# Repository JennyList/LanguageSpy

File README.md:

# LanguageSpy
Open source code from Language Spy, [http://www.languagespy.com](http://www.languagespy.com)

The Hardware directory contains open source hardware projects.

The RaspberryPi directory contains code for the Raspberry Pi.

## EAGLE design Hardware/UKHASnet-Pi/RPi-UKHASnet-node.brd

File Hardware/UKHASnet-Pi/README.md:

# A HopeRF RFM69 board for the Raspberry Pi
This is a board to allow the [HopeRF RFM69](http://www.hoperf.com/rf_transceiver/modules/RFM69HW.html) RF modules to be interfaced to a Raspberry Pi. It can be used for experimenting with [UKHASnet](https://ukhas.net/), or just as an experimenting board in its own right for the RFM69 series.

###Files:
- RPi-UKHASnet-node.brd, an EAGLE CAD board file.
- RPi-UKHASnet-node.sch, an EAGLE CAD schematic file.
- UKHASnet-node-gerbers.zip, Gerber files for manufacturing generated through EAGLE CAD using Dirt Cheap Dirty Boards' CAM file.
- UKHASnet-Pi-board.png, a generated image of the PCB.
- UKHASnet-Pi-schematic.png, the converter circuit diagram.
- LICENCE, a copy of the Solderpad Hardware Licence v0.51

###Description:
This is a simple breakout board, very little rocket science. It features a 3.3v regulator on the underside because the module is capable of taking more current than the Pi's regulator has to spare.

###Licence and boilerplate

This project is licenced under the Solderpad Hardware licence.

Copyright 2016 Jenny List
Copyright and related rights are licensed under the Solderpad Hardware License, Version 0.51 (the “License”); you may not use these files except in compliance with the License. 
You may obtain a copy of the License at [http://solderpad.org/licenses/SHL-0.51](http://solderpad.org/licenses/SHL-0.51). Unless required by applicable law or agreed to in writing, software, hardware and materials distributed under this License is distributed on an “AS IS” BASIS, WITHOUT WARRANTIES OR CONDITIONS OF ANY KIND, either express or implied. See the License for the specific language governing permissions and limitations under the License.

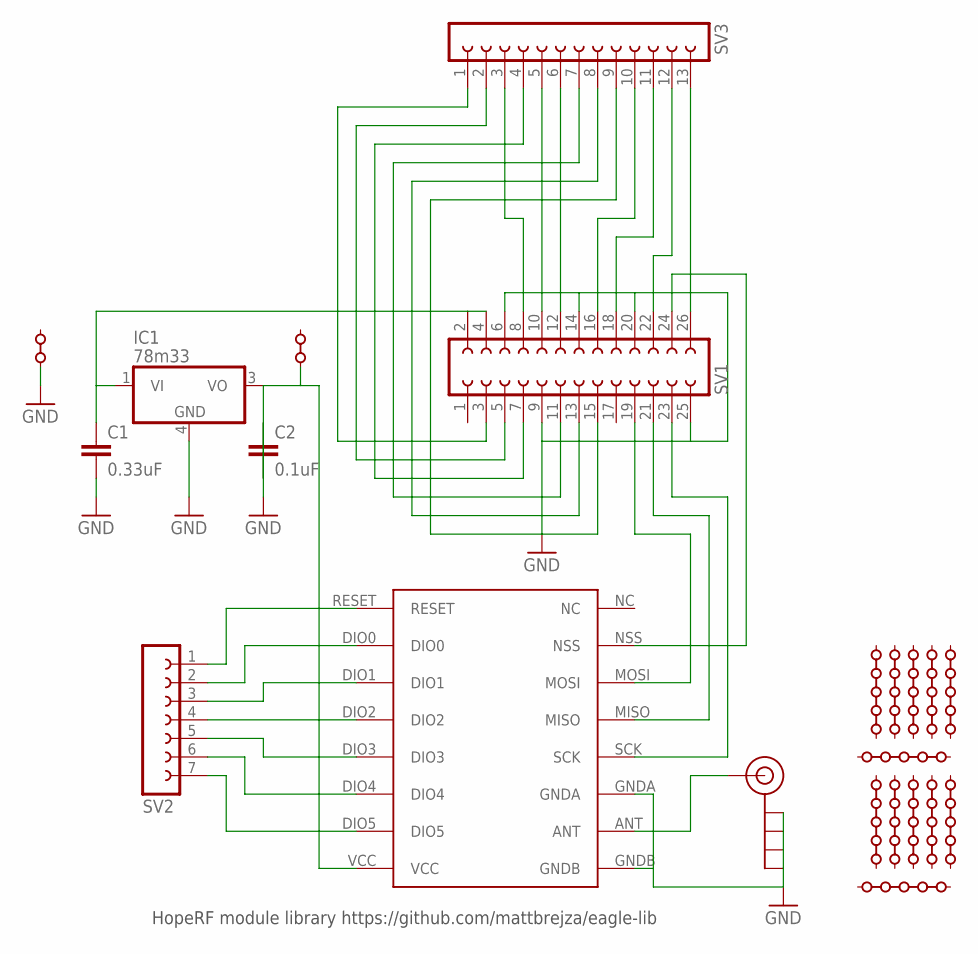
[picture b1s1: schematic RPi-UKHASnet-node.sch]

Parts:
C1: 0.33uF; C1206
C2: 0.1uF; C1206
IC1: 78m33; SOT223
J$1: SMA_EDGE; SMA-EDGE
P1, P2, P3, P4, P5, P9, P10, P11, P12, P13, P17, P18: PADSTRIP5-VA; PADSTRIP-5V
PR8, PR20: PADSTRIP2-H; PADSTRIP-2H
SV1: FE13-2
SV2: FE07-1; FE07
SV3: FE13-1; FE13
U1: RFM69HW; RFM

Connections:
GND: C1.2, C2.1, IC1.4 (GND), J$1.GND@0 (GND), J$1.GND@1 (GND), J$1.GND@2 (GND), J$1.GND@3 (GND), PR20.1 (LFT), SV1.6, SV1.9, SV1.14, SV1.20, SV1.25, U1.GNDA, U1.GNDB
unnamed: J$1.SIG (SIGNAL), U1.ANT
unnamed: SV2.7, U1.DIO5
unnamed: SV2.6, U1.DIO4
unnamed: SV2.5, U1.DIO3
unnamed: SV2.4, U1.DIO2
unnamed: SV2.3, U1.DIO1
unnamed: SV2.2, U1.DIO0
unnamed: SV1.24, U1.NSS
unnamed: SV1.23, U1.SCK
unnamed: SV1.21, U1.MISO
unnamed: SV1.19, U1.MOSI
unnamed: SV1.3, SV3.1
unnamed: C1.1, IC1.1 (VI), SV1.2, SV1.4
unnamed: C2.2, IC1.3 (VO), PR8.1 (LFT), U1.VCC
unnamed: SV2.1, U1.RESET
unnamed: SV1.5, SV3.2
unnamed: SV1.7, SV3.4
unnamed: SV1.11, SV3.7
unnamed: SV1.13, SV3.8
unnamed: SV1.15, SV3.9
unnamed: SV1.8, SV3.3
unnamed: SV1.10, SV3.5
unnamed: SV1.12, SV3.6
unnamed: SV1.16, SV3.10
unnamed: SV1.18, SV3.11
unnamed: SV1.22, SV3.12
unnamed: SV1.26, SV3.13

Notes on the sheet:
HopeRF module library https://github.com/mattbrejza/eagle-lib

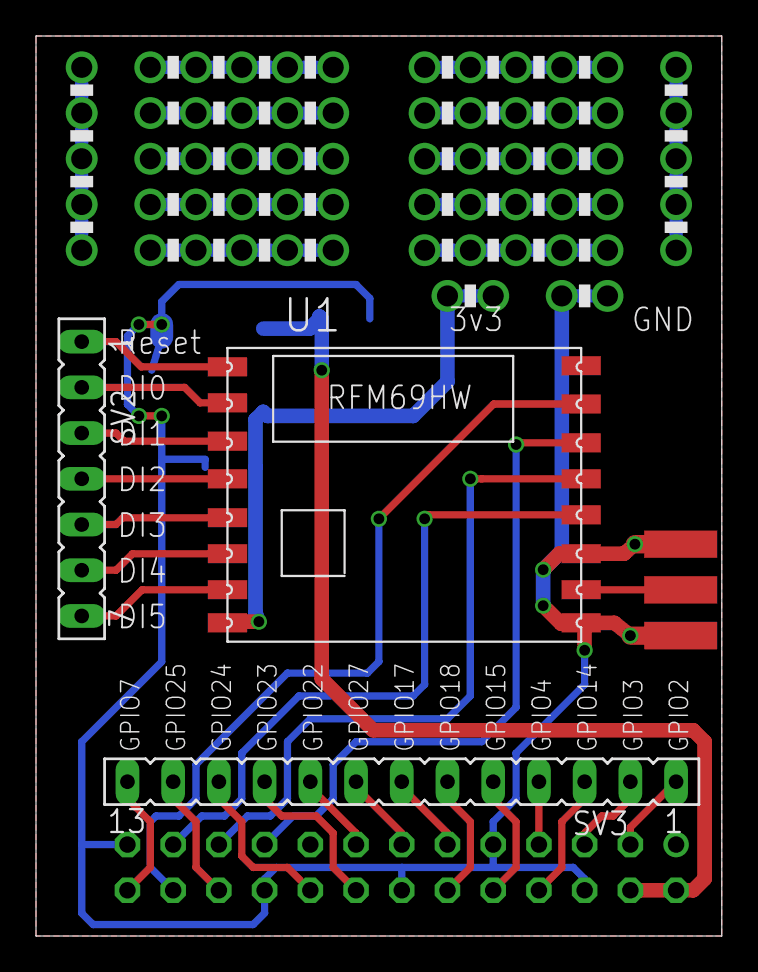
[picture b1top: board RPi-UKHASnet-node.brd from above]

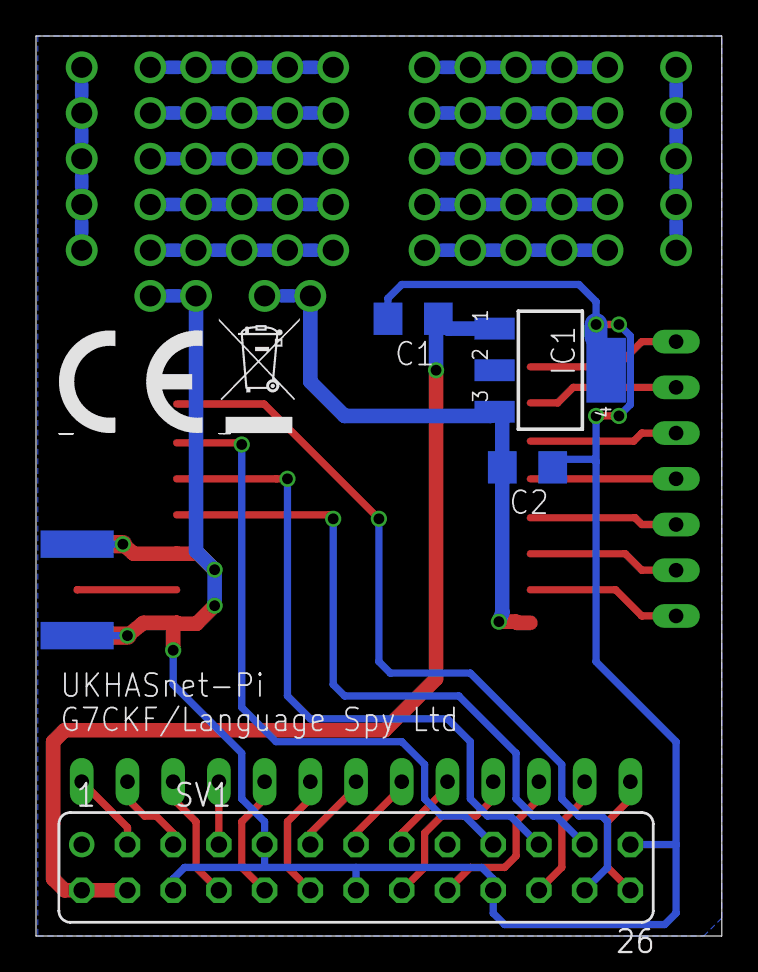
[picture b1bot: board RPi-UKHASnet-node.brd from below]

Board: 2 copper layers, 38.1 x 50.0 mm, 24 parts (6 on the bottom side), 28 nets.

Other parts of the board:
U$2: CE-LOGO
U$3: WEE-LOGO

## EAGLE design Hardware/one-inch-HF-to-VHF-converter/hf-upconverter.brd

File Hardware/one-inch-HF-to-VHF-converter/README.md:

# One inch HF to VHF converter
This is an entry for the [2015 Hackaday.io One Square Inch competition](https://hackaday.io/project/7813-the-square-inch-project), an HF receive converter for VHF receivers like the RTL SDR or similar. You can find its project page [here](https://hackaday.io/project/8486-hf-receive-converter-for-rtl-sdrs-and-similar).

###Files:
- hf-upconverter.brd, an EAGLE CAD board file.
- hf-upconverter.sch, an EAGLE CAD schematic file.
- one-inch-HF-receive-converter-gerbers-v1.2.zip, Gerber files for manufacturing generated through EAGLE CAD using OSH Park's CAM file.
- upconverter PCB.png, a generated image of the PCB.
- upconverter schematic.png, the converter circuit diagram.
- hf-upconverter-bom.csv, the bill of materials for the project.
- LICENCE, a copy of the Solderpad Hardware Licence v0.51

###Instructions:
It's a small board, so the instructions are short and sweet.
Solder all the chip components first, then the mixer IC, then the transformer, the electrolytic, the oscillator, and finally the connectors. You'll get lots of flux all over everything, but a quick brush with a bit of solvent cleaner should deal with that.

###Licence and boilerplate

This project is licenced under the Solderpad Hardware licence.

Copyright 2015 Jenny List
Copyright and related rights are licensed under the Solderpad Hardware License, Version 0.51 (the “License”); you may not use these files except in compliance with the License. 
You may obtain a copy of the License at [http://solderpad.org/licenses/SHL-0.51](http://solderpad.org/licenses/SHL-0.51). Unless required by applicable law or agreed to in writing, software, hardware and materials distributed under this License is distributed on an “AS IS” BASIS, WITHOUT WARRANTIES OR CONDITIONS OF ANY KIND, either express or implied. See the License for the specific language governing permissions and limitations under the License.

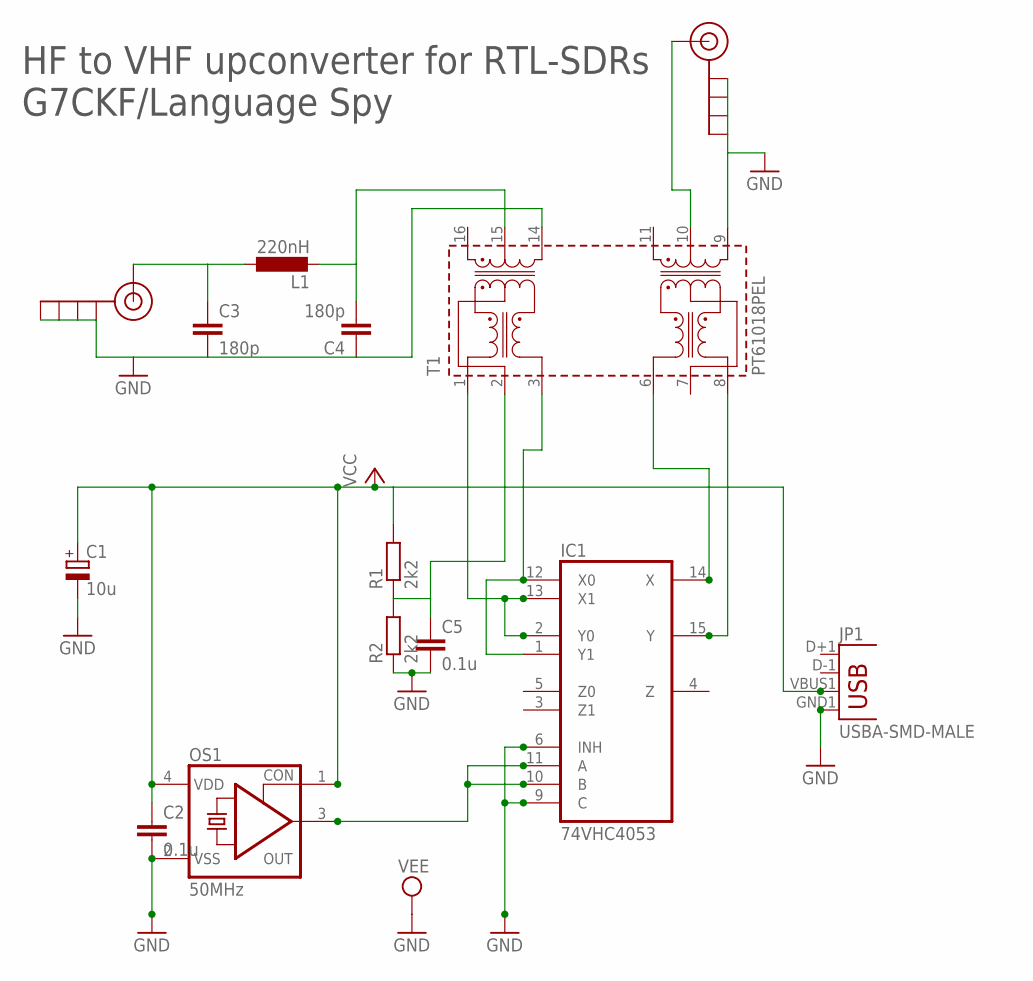
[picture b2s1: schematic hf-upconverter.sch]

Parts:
C1: 10u; PANASONIC_B
C2, C5: 0.1u; C0805
C3, C4: 180p; C0805
IC1: 74VHC4053; SO16
JP1: USBA-SMD-MALE; USB-A-SMT-MALE
L1: 220nH; R1206
OS1: 50MHz; 7.2X5.2-4-PAD
R1, R2: 2k2; R0805
SMA1: ANT; SMA-EDGE
SMA2: OUT; SMA-EDGE
T1: PT61018PEL; N5

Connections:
GND: C1.-, C2.2, C3.2, C4.1, C5.2, IC1.6 (INH), IC1.7 (VEE), IC1.8 (GND), IC1.9 (C), JP1.GND1 (GND), OS1.2 (VSS), R2.1, SMA1.GND@0 (GND), SMA1.GND@1 (GND), SMA1.GND@2 (GND), SMA1.GND@3 (GND), SMA2.GND@0 (GND), SMA2.GND@1 (GND), SMA2.GND@2 (GND), SMA2.GND@3 (GND), T1.9, T1.14
unnamed: IC1.10 (B), IC1.11 (A), OS1.3 (OUT)
unnamed: C5.1, R1.1, R2.2, T1.2
unnamed: IC1.1 (Y1), IC1.12 (X0), T1.3
unnamed: IC1.2 (Y0), IC1.13 (X1), T1.1
unnamed: C3.1, L1.1, SMA1.SIG (SIGNAL)
unnamed: IC1.14 (X), T1.6
unnamed: IC1.15 (Y), T1.8
unnamed: C4.2, L1.2, T1.15
unnamed: SMA2.SIG (SIGNAL), T1.10
VCC: C1.+, C2.1, IC1.16 (VCC), JP1.VBUS1 (VBUS), OS1.1 (CON), OS1.4 (VDD), R1.2

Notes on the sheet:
HF to VHF upconverter for RTL-SDRs G7CKF/Language Spy

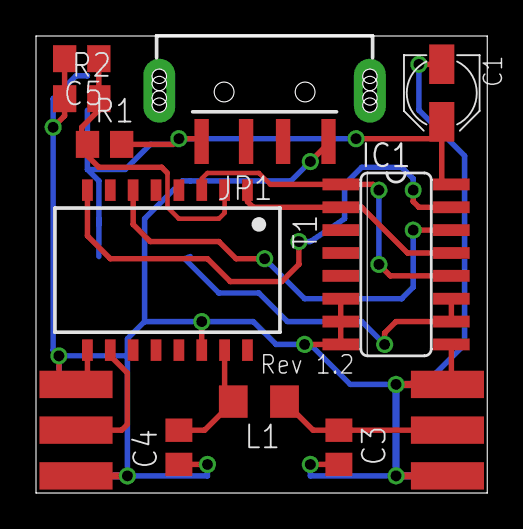
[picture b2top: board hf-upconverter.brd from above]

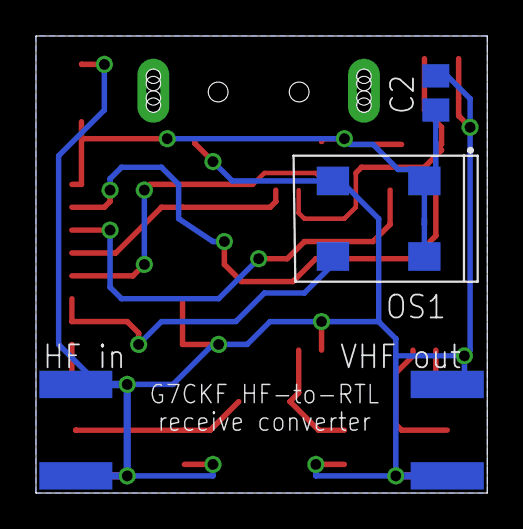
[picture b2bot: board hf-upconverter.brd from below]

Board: 2 copper layers, 25.1 x 25.4 mm, 14 parts (2 on the bottom side), 11 nets.

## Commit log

2015-07-04 Added freq_pi version for RPi 2
2015-07-05 Updated version number to 0.71
2015-07-09 added Raspberry Pi SSTV proof-of-concept code
2015-07-09 Updated README files
2015-10-16 Updated to version 0.71 with automatic detection of Raspberry Pi boards
2015-10-16 First upload of version 0.1 of PiVFO
2015-10-16 Updated with clearer instructions and new versions of freq_pi and PiVFO
2015-10-16 freq_pi version updated to 0.72
2015-10-16 Readme edited to tidy markdown
2015-10-18 Added a quick install section
2015-10-18 Small markdown tidy in README
2015-11-20 Hardware tree added, HF receive converter added.
2015-11-24 Small schematic symbol change in HF upconverter
2015-12-06 Fresh HF upconverter Gerbers
2015-12-20 Updated PCB to v1.2, with SMA connector centre pins on top of the board.
2015-12-20 README spelling fix
2016-03-13 Updated READMEs for new Pi, added UKHASnet board
2025-12-24 Uploading docs for Language Spy kits

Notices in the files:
parts and their libraries:
SparkFun-Connectors: Licensing: Creative Commons ShareAlike 4.0 International - https://creativecommons.org/licenses/by-sa/4.0
